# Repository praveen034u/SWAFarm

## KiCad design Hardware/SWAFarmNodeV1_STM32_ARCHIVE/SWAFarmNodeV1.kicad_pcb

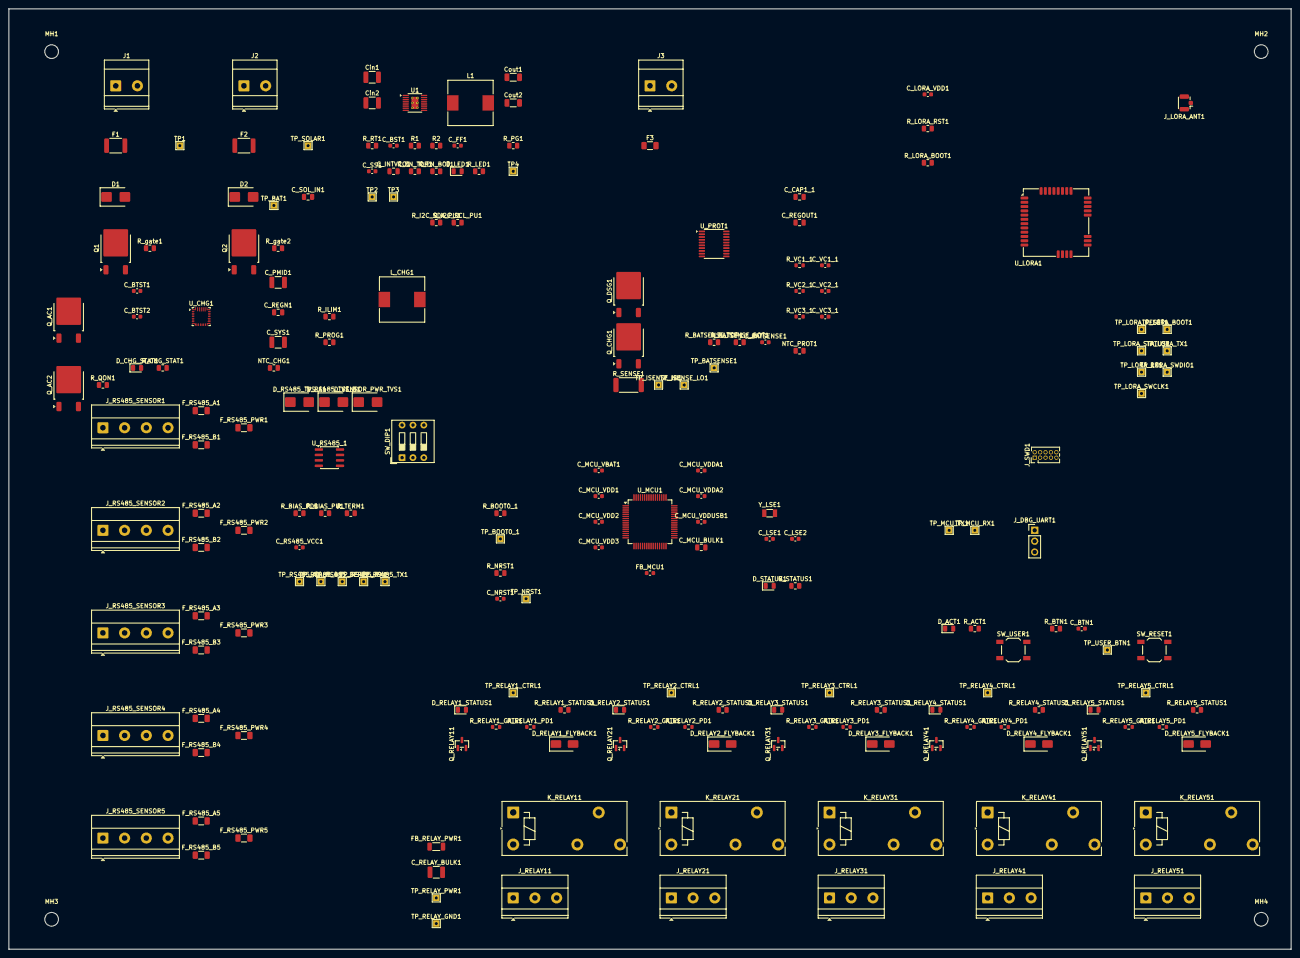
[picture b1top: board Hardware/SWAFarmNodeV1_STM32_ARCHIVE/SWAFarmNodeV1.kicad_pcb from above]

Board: 4 copper layers, 300.0 x 220.0 mm, 203 parts (0 on the bottom side), 138 nets, no tracks yet.

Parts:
C_BATSENSE1: 100nF; C_0603_1608Metric
C_BST1: 0.1uF; C_0603_1608Metric
C_BTN1: 100nF; C_0603_1608Metric
C_BTST1, C_BTST2: 100nF; C_0603_1608Metric
C_CAP1_1: 1uF; C_0805_2012Metric
C_FF1: 10pF; C_0603_1608Metric
C_INTVCC1: 2.2uF; C_0805_2012Metric
C_LORA_VDD1: 100nF; C_0603_1608Metric
C_LSE1, C_LSE2: 8pF; C_0603_1608Metric
C_MCU_BULK1: 4.7uF; C_0805_2012Metric
C_MCU_VBAT1: 100nF; C_0603_1608Metric
C_MCU_VDD1, C_MCU_VDD2, C_MCU_VDD3: 100nF; C_0603_1608Metric
C_MCU_VDDA1: 1uF; C_0603_1608Metric
C_MCU_VDDA2: 100nF; C_0603_1608Metric
C_MCU_VDDUSB1: 100nF; C_0603_1608Metric
C_NRST1: 100nF; C_0603_1608Metric
C_PMID1: 10uF; C_1210_3225Metric
C_REGN1: 1uF; C_0805_2012Metric
C_REGOUT1: 1uF; C_0805_2012Metric
C_RELAY_BULK1: 22uF; C_1210_3225Metric
C_RS485_VCC1: 100nF; C_0603_1608Metric
C_SOL_IN1: 4.7uF; C_0805_2012Metric
C_SS1: 10nF; C_0603_1608Metric
C_SYS1: 22uF; C_1210_3225Metric
C_VC1_1, C_VC2_1, C_VC3_1: 100nF; C_0603_1608Metric
Cin1, Cin2: 10uF_50V; C_1210_3225Metric
Cout1, Cout2: 22uF_16V; C_1206_3216Metric
D1: SMBJ16CA; D_SMB
D2: SMBJ24A_class_unidirectional; D_SMB
D_ACT1: LED_Yellow_activity; LED_0805_2012Metric
D_CHG_STAT1: LED_Yellow_charge_status; LED_0805_2012Metric
D_LED1: LED_Green_2mA; LED_0805_2012Metric
D_RELAY1_FLYBACK1, D_RELAY2_FLYBACK1, D_RELAY3_FLYBACK1, D_RELAY4_FLYBACK1, D_RELAY5_FLYBACK1: S1M_1A_1000V_SMA; D_SMA
D_RELAY1_STATUS1, D_RELAY2_STATUS1, D_RELAY3_STATUS1, D_RELAY4_STATUS1, D_RELAY5_STATUS1: LED_Green_relay_status; LED_0805_2012Metric
D_RS485_TVS_A1, D_RS485_TVS_B1: SMBJ_class_RS485; D_SMB
D_SENSOR_PWR_TVS1: SMBJ18A_class_unidirectional; D_SMB
D_STATUS1: LED_Green_status; LED_0805_2012Metric
F1: 1.1A_Hold_PTC; Fuse_1812_4532Metric
F2: 0.75A_Hold_PTC; Fuse_1812_4532Metric
F3: 10A_series_onetime; Fuse_1206_3216Metric
FB_MCU1: BLM18 class; L_0603_1608Metric
FB_RELAY_PWR1: Power Ferrite, 1A class; L_1206_3216Metric
F_RS485_A1, F_RS485_A2, F_RS485_A3, F_RS485_A4, F_RS485_A5, F_RS485_B1, F_RS485_B2, F_RS485_B3, F_RS485_B4, F_RS485_B5, F_RS485_PWR1, F_RS485_PWR2, F_RS485_PWR3, F_RS485_PWR4, F_RS485_PWR5: 0.2A_Hold_PTC; Fuse_1206_3216Metric
J1: DC_IN_12V; TerminalBlock_Phoenix_MKDS-3-2-5.08_1x02_P5.08mm_Horizontal
J2: SOLAR_IN_12V_class; TerminalBlock_Phoenix_MKDS-3-2-5.08_1x02_P5.08mm_Horizontal
J3: 4S_LiFePO4_Pack; TerminalBlock_Phoenix_MKDS-3-2-5.08_1x02_P5.08mm_Horizontal
J_DBG_UART1: Debug_Console; PinHeader_1x03_P2.54mm_Vertical
J_LORA_ANT1: U.FL_to_SMA_pigtail; U.FL_Hirose_U.FL-R-SMT-1_Vertical
J_RELAY11: Relay1_COM_NO_NC; TerminalBlock_Phoenix_MKDS-1,5-3-5.08_1x03_P5.08mm_Horizont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
J_RELAY21: Relay2_COM_NO_NC; TerminalBlock_Phoenix_MKDS-1,5-3-5.08_1x03_P5.08mm_Horizont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
J_RELAY31: Relay3_COM_NO_NC; TerminalBlock_Phoenix_MKDS-1,5-3-5.08_1x03_P5.08mm_Horizont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
J_RELAY41: Relay4_COM_NO_NC; TerminalBlock_Phoenix_MKDS-1,5-3-5.08_1x03_P5.08mm_Horizont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
J_RELAY51: Relay5_COM_NO_NC; TerminalBlock_Phoenix_MKDS-1,5-3-5.08_1x03_P5.08mm_Horizont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
J_RS485_SENSOR1: Sensor1_A_B_PWR_GND; TerminalBlock_Phoenix_MKDS-1,5-4-5.08_1x04_P5.08mm_Horizont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
J_RS485_SENSOR2: Sensor2_A_B_PWR_GND; TerminalBlock_Phoenix_MKDS-1,5-4-5.08_1x04_P5.08mm_Horizont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
J_RS485_SENSOR3: Sensor3_A_B_PWR_GND; TerminalBlock_Phoenix_MKDS-1,5-4-5.08_1x04_P5.08mm_Horizont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
J_RS485_SENSOR4: Sensor4_A_B_PWR_GND; TerminalBlock_Phoenix_MKDS-1,5-4-5.08_1x04_P5.08mm_Horizont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
J_RS485_SENSOR5: Sensor5_A_B_PWR_GND; TerminalBlock_Phoenix_MKDS-1,5-4-5.08_1x04_P5.08mm_Horizont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
J_SWD1: SWD_ARM10; PinHeader_2x05_P1.27mm_Vertical
K_RELAY11, K_RELAY21, K_RELAY31, K_RELAY41, K_RELAY51: FINDER-40.51.9.012.0000_12VDC_SPDT_10A; Relay_SPDT_Finder_40.51
L1: 4.7uH; L_10.4x10.4_H4.8
L_CHG1: 2.2uH_5A_class; L_10.4x10.4_H4.8
MH1, MH2, MH3, MH4: MountingHole_3.2mm_M3
NTC_CHG1: 10k_NTC_-20to60C_class; R_0805_2012Metric
NTC_PROT1: 10k_NTC_-20to60C_class; R_0805_2012Metric
Q1, Q2: NMOS_30V_RDSon_20mOhm; TO-252-2
Q_AC1, Q_AC2: NMOS_30V_RDSon_20mOhm; TO-252-2
Q_CHG1: NMOS_30V_RDSon_20mOhm; TO-252-2
Q_DSG1: NMOS_30V_RDSon_20mOhm; TO-252-2
Q_RELAY11, Q_RELAY21, Q_RELAY31, Q_RELAY41, Q_RELAY51: NMOS_30V_RDSon_100mOhm_SOT23; SOT-23
R1: 24.0k_1%; R_0805_2012Metric
R2: 10.0k_1%; R_0805_2012Metric
R_ACT1: 1k; R_0805_2012Metric
R_BATSENSE_BOT1: 180k; R_0805_2012Metric
R_BATSENSE_TOP1: 680k; R_0805_2012Metric
R_BIAS_PD1: 560; R_0805_2012Metric
R_BIAS_PU1: 560; R_0805_2012Metric
R_BOOT0_1: 10k; R_0805_2012Metric
R_BTN1: 10k; R_0805_2012Metric
R_CHG_STAT1: 1k; R_0805_2012Metric
R_EN_BOT1: 100k; R_0805_2012Metric
R_EN_TOP1: 787k; R_0805_2012Metric
R_I2C_SCL_PU1, R_I2C_SDA_PU1: 4.7k; R_0805_2012Metric
R_ILIM1: TBD_verify_datasheet_ILIM_formula; R_0805_2012Metric
R_LED1: 680; R_0805_2012Metric
R_LORA_BOOT1: 10k; R_0805_2012Metric
R_LORA_RST1: 10k; R_0805_2012Metric
R_NRST1: 10k; R_0805_2012Metric
R_PG1: 100k; R_0805_2012Metric
R_PROG1: TBD_verify_datasheet_for_1.6A_target; R_0805_2012Metric
R_QON1: 100k; R_0805_2012Metric
R_RELAY1_GATE1, R_RELAY2_GATE1, R_RELAY3_GATE1, R_RELAY4_GATE1, R_RELAY5_GATE1: 100; R_0603_1608Metric
R_RELAY1_PD1, R_RELAY2_PD1, R_RELAY3_PD1, R_RELAY4_PD1, R_RELAY5_PD1: 10k; R_0603_1608Metric
R_RELAY1_STATUS1, R_RELAY2_STATUS1, R_RELAY3_STATUS1, R_RELAY4_STATUS1, R_RELAY5_STATUS1: 1k; R_0805_2012Metric
R_RT1: 41.2k; R_0805_2012Metric
R_SENSE1: 5mOhm_1percent_2512; R_2512_6332Metric
R_STATUS1: 330; R_0805_2012Metric
R_TERM1: 120; R_0805_2012Metric
R_VC1_1, R_VC2_1, R_VC3_1: 1k; R_0603_1608Metric
R_gate1, R_gate2: 10k; R_0805_2012Metric
SW_DIP1: TERM_BIAS_SELECT; SW_DIP_SPSTx03_Slide_9.78x9.8mm_W7.62mm_P2.54mm
SW_RESET1: Reset_Button; SW_SPST_TL3342
SW_USER1: User_Button; SW_SPST_TL3342
TP1: VIN_PROT; TestPoint_THTPad_1.5x1.5mm_Drill0.7mm
TP2: 3V3_RAIL; TestPoint_THTPad_1.5x1.5mm_Drill0.7mm
TP3: GND; TestPoint_THTPad_1.5x1.5mm_Drill0.7mm
TP4: PG; TestPoint_THTPad_1.5x1.5mm_Drill0.7mm
TP_BAT1: BAT_P; TestPoint_THTPad_1.5x1.5mm_Drill0.7mm
TP_BATSENSE1: BATSENSE_MID; TestPoint_THTPad_1.5x1.5mm_Drill0.7mm
TP_BOOT0_1: BOOT0; TestPoint_THTPad_1.5x1.5mm_Drill0.7mm
TP_ISENSE_HI1: SRP; TestPoint_THTPad_1.5x1.5mm_Drill0.7mm
TP_ISENSE_LO1: SRN_GND; TestPoint_THTPad_1.5x1.5mm_Drill0.7mm
TP_LORA_BOOT1: LORA_BOOT0; TestPoint_THTPad_1.5x1.5mm_Drill0.7mm
TP_LORA_RESET1: LORA_RESET_N; TestPoint_THTPad_1.5x1.5mm_Drill0.7mm
TP_LORA_RX1: LORA_RX; TestPoint_THTPad_1.5x1.5mm_Drill0.7mm
TP_LORA_STATUS1: LORA_STATUS; TestPoint_THTPad_1.5x1.5mm_Drill0.7mm
TP_LORA_SWCLK1: LORA_SWCLK; TestPoint_THTPad_1.5x1.5mm_Drill0.7mm
TP_LORA_SWDIO1: LORA_SWDIO; TestPoint_THTPad_1.5x1.5mm_Drill0.7mm
TP_LORA_TX1: LORA_TX; TestPoint_THTPad_1.5x1.5mm_Drill0.7mm
TP_MCU_RX1: MCU_RX; TestPoint_THTPad_1.5x1.5mm_Drill0.7mm
TP_MCU_TX1: MCU_TX; TestPoint_THTPad_1.5x1.5mm_Drill0.7mm
TP_NRST1: NRST; TestPoint_THTPad_1.5x1.5mm_Drill0.7mm
TP_RELAY1_CTRL1: RELAY1_CTRL; TestPoint_THTPad_1.5x1.5mm_Drill0.7mm
TP_RELAY2_CTRL1: RELAY2_CTRL; TestPoint_THTPad_1.5x1.5mm_Drill0.7mm
TP_RELAY3_CTRL1: RELAY3_CTRL; TestPoint_THTPad_1.5x1.5mm_Drill0.7mm
TP_RELAY4_CTRL1: RELAY4_CTRL; TestPoint_THTPad_1.5x1.5mm_Drill0.7mm
TP_RELAY5_CTRL1: RELAY5_CTRL; TestPoint_THTPad_1.5x1.5mm_Drill0.7mm
TP_RELAY_GND1: GND; TestPoint_THTPad_1.5x1.5mm_Drill0.7mm
TP_RELAY_PWR1: RELAY_PWR; TestPoint_THTPad_1.5x1.5mm_Drill0.7mm
TP_RS485_A1: RS485_A; TestPoint_THTPad_1.5x1.5mm_Drill0.7mm
TP_RS485_B1: RS485_B; TestPoint_THTPad_1.5x1.5mm_Drill0.7mm
TP_RS485_DERE1: RS485_DE_RE; TestPoint_THTPad_1.5x1.5mm_Drill0.7mm
TP_RS485_RX1: RS485_RX; TestPoint_THTPad_1.5x1.5mm_Drill0.7mm
TP_RS485_TX1: RS485_TX; TestPoint_THTPad_1.5x1.5mm_Drill0.7mm
TP_SOLAR1: SOL_PROT; TestPoint_THTPad_1.5x1.5mm_Drill0.7mm
TP_USER_BTN1: USER_BTN; TestPoint_THTPad_1.5x1.5mm_Drill0.7mm
U1: LT8610AC-3.3; MSOP-16-1EP_3x4.039mm_P0.5mm_EP1.651x2.845mm_ThermalVias
U_CHG1: BQ25798_substitutes_BQ25792; Texas_RQM0029A_VQFN-29_4x4mm_P0.4mm
U_LORA1: RAK3172-IN865; RAK3172
U_MCU1: STM32L462RETx; LQFP-64_10x10mm_P0.5mm
U_PROT1: BQ76920PW; TSSOP-20_4.4x6.5mm_P0.65mm
U_RS485_1: THVD1450D; SOIC-8_3.9x4.9mm_P1.27mm
Y_LSE1: 32.768kHz; Crystal_SMD_3215-2Pin_3.2x1.5mm

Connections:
/3V3_RAIL: C_FF1.1, C_LORA_VDD1.1, C_MCU_BULK1.1, C_MCU_VBAT1.1, C_MCU_VDD1.1, C_MCU_VDD2.1, C_MCU_VDD3.1, C_MCU_VDDUSB1.1, C_RS485_VCC1.1, Cout1.1, Cout2.1, FB_MCU1.1, J_SWD1.1, L1.1, R1.1, R_BIAS_PU1.2, R_BTN1.1, R_CHG_STAT1.1, R_I2C_SCL_PU1.1, R_I2C_SDA_PU1.1, R_LED1.1, R_LORA_RST1.1, R_NRST1.1, R_PG1.1, TP2.1, U1.14, U_LORA1.24, U_MCU1.1, U_MCU1.19, U_MCU1.32, U_MCU1.48, U_MCU1.64, U_RS485_1.8
/ACTIVITY_LED: R_ACT1.1, U_MCU1.39
/BATSENSE_MID: C_BATSENSE1.1, R_BATSENSE_BOT1.1, R_BATSENSE_TOP1.2, TP_BATSENSE1.1, U_MCU1.27
/BAT_P: F3.2, R_BATSENSE_TOP1.1, TP_BAT1.1, U_CHG1.18, U_CHG1.22, U_CHG1.23, U_PROT1.9, U_PROT1.10, U_PROT1.12, U_PROT1.13
/BOOT0: R_BOOT0_1.1, TP_BOOT0_1.1, U_MCU1.60
/BTST1_NODE: C_BTST1.1, U_CHG1.4
/BTST2_NODE: C_BTST2.1, U_CHG1.19
/CAP1_NODE: C_CAP1_1.1, U_PROT1.7
/CELL_N: J3.2, Q_DSG1.3, U_PROT1.17
/CELL_TAP1: R_VC1_1.1, U_PROT1.16
/CELL_TAP1_FILT: C_VC1_1.1, R_VC1_1.2
/CELL_TAP2: R_VC2_1.1, U_PROT1.15
/CELL_TAP2_FILT: C_VC2_1.1, R_VC2_1.2
/CELL_TAP3: R_VC3_1.1, U_PROT1.14
/CELL_TAP3_FILT: C_VC3_1.1, R_VC3_1.2
/CHG_ALERT_N: U_CHG1.21, U_MCU1.24
/CHG_STAT: D_CHG_STAT1.2, R_CHG_STAT1.2, U_CHG1.1
/CHG_VBUS_INT: C_BTST1.2, C_BTST2.2, Q_AC1.2, Q_AC2.2, U_CHG1.2, U_CHG1.3
/DC_IN_RAW_N: J1.2, Q1.3
/DC_IN_RAW_P: F1.1, J1.1
/FET_MID: Q_CHG1.2, Q_DSG1.2
/J3_BAT_P_RAW: F3.1, J3.1
/LORA_BOOT0: R_LORA_BOOT1.1, TP_LORA_BOOT1.1, U_LORA1.21
/LORA_RESET_N: R_LORA_RST1.2, TP_LORA_RESET1.1, U_LORA1.22, U_MCU1.14
/LORA_RX: TP_LORA_RX1.1, U_LORA1.4, U_MCU1.17
/LORA_STATUS: TP_LORA_STATUS1.1, U_LORA1.32, U_MCU1.15
/LORA_SWCLK: TP_LORA_SWCLK1.1, U_LORA1.8
/LORA_SWDIO: TP_LORA_SWDIO1.1, U_LORA1.7
/LORA_TX: TP_LORA_TX1.1, U_LORA1.5, U_MCU1.16
/MCU_RX: J_DBG_UART1.3, TP_MCU_RX1.1, U_MCU1.43
/MCU_TX: J_DBG_UART1.2, TP_MCU_TX1.1, U_MCU1.42
/NET_CHG_GATE: Q_CHG1.1, U_PROT1.2
/NET_CHG_SW1: L_CHG1.1, U_CHG1.28
/NET_CHG_SW2: L_CHG1.2, U_CHG1.26
/NET_DSG_GATE: Q_DSG1.1, U_PROT1.1
/NET_ILIM_HIZ: R_ILIM1.1, U_CHG1.17
/NET_PROG: R_PROG1.1, U_CHG1.20
/NET_Q2_GATE: Q2.1, R_gate2.2
/NET_QAC1_GATE: Q_AC1.1, U_CHG1.11
/NET_QAC2_GATE: Q_AC2.1, U_CHG1.10
/NET_QON: R_QON1.1, U_CHG1.12
/NRST: C_NRST1.1, J_SWD1.10, R_NRST1.2, SW_RESET1.1, TP_NRST1.1, U_MCU1.7
/NTC_CHG_NODE: NTC_CHG1.1, U_CHG1.16
/NTC_PROT_NODE: NTC_PROT1.1, U_PROT1.6
/OSC32_IN: C_LSE1.1, U_MCU1.3, Y_LSE1.1
/OSC32_OUT: C_LSE2.1, U_MCU1.4, Y_LSE1.2
/PG: R_PG1.2, TP4.1, U1.15
/PMID_NODE: C_PMID1.1, U_CHG1.29
/PROT_ALERT_N: U_MCU1.25, U_PROT1.20
/PWR_I2C_SCL: R_I2C_SCL_PU1.2, U_CHG1.14, U_MCU1.61, U_PROT1.5
/PWR_I2C_SDA: R_I2C_SDA_PU1.2, U_CHG1.15, U_MCU1.62, U_PROT1.4
/REGN_NODE: C_REGN1.1, U_CHG1.5
/REGOUT_NODE: C_REGOUT1.1, U_PROT1.8
/RELAY1_COIL_RTN: D_RELAY1_FLYBACK1.2, K_RELAY11.A2, Q_RELAY11.3
/RELAY1_COM: J_RELAY11.1, K_RELAY11.11
/RELAY1_CTRL: R_RELAY1_GATE1.1, R_RELAY1_STATUS1.1, TP_RELAY1_CTRL1.1, U_MCU1.33
/RELAY1_GATE: Q_RELAY11.1, R_RELAY1_GATE1.2, R_RELAY1_PD1.1
/RELAY1_LED_A: D_RELAY1_STATUS1.2, R_RELAY1_STATUS1.2
/RELAY1_NC: J_RELAY11.3, K_RELAY11.12
/RELAY1_NO: J_RELAY11.2, K_RELAY11.14
/RELAY2_COIL_RTN: D_RELAY2_FLYBACK1.2, K_RELAY21.A2, Q_RELAY21.3
/RELAY2_COM: J_RELAY21.1, K_RELAY21.11
/RELAY2_CTRL: R_RELAY2_GATE1.1, R_RELAY2_STATUS1.1, TP_RELAY2_CTRL1.1, U_MCU1.34
/RELAY2_GATE: Q_RELAY21.1, R_RELAY2_GATE1.2, R_RELAY2_PD1.1
/RELAY2_LED_A: D_RELAY2_STATUS1.2, R_RELAY2_STATUS1.2
/RELAY2_NC: J_RELAY21.3, K_RELAY21.12
/RELAY2_NO: J_RELAY21.2, K_RELAY21.14
/RELAY3_COIL_RTN: D_RELAY3_FLYBACK1.2, K_RELAY31.A2, Q_RELAY31.3
/RELAY3_COM: J_RELAY31.1, K_RELAY31.11
/RELAY3_CTRL: R_RELAY3_GATE1.1, R_RELAY3_STATUS1.1, TP_RELAY3_CTRL1.1, U_MCU1.35
/RELAY3_GATE: Q_RELAY31.1, R_RELAY3_GATE1.2, R_RELAY3_PD1.1
/RELAY3_LED_A: D_RELAY3_STATUS1.2, R_RELAY3_STATUS1.2
/RELAY3_NC: J_RELAY31.3, K_RELAY31.12
/RELAY3_NO: J_RELAY31.2, K_RELAY31.14
/RELAY4_COIL_RTN: D_RELAY4_FLYBACK1.2, K_RELAY41.A2, Q_RELAY41.3
/RELAY4_COM: J_RELAY41.1, K_RELAY41.11
/RELAY4_CTRL: R_RELAY4_GATE1.1, R_RELAY4_STATUS1.1, TP_RELAY4_CTRL1.1, U_MCU1.36
/RELAY4_GATE: Q_RELAY41.1, R_RELAY4_GATE1.2, R_RELAY4_PD1.1
/RELAY4_LED_A: D_RELAY4_STATUS1.2, R_RELAY4_STATUS1.2
/RELAY4_NC: J_RELAY41.3, K_RELAY41.12
/RELAY4_NO: J_RELAY41.2, K_RELAY41.14
/RELAY5_COIL_RTN: D_RELAY5_FLYBACK1.2, K_RELAY51.A2, Q_RELAY51.3
/RELAY5_COM: J_RELAY51.1, K_RELAY51.11
/RELAY5_CTRL: R_RELAY5_GATE1.1, R_RELAY5_STATUS1.1, TP_RELAY5_CTRL1.1, U_MCU1.50
/RELAY5_GATE: Q_RELAY51.1, R_RELAY5_GATE1.2, R_RELAY5_PD1.1
/RELAY5_LED_A: D_RELAY5_STATUS1.2, R_RELAY5_STATUS1.2
/RELAY5_NC: J_RELAY51.3, K_RELAY51.12
/RELAY5_NO: J_RELAY51.2, K_RELAY51.14
/RELAY_PWR: C_RELAY_BULK1.1, D_RELAY1_FLYBACK1.1, D_RELAY2_FLYBACK1.1, D_RELAY3_FLYBACK1.1, D_RELAY4_FLYBACK1.1, D_RELAY5_FLYBACK1.1, FB_RELAY_PWR1.2, K_RELAY11.A1, K_RELAY21.A1, K_RELAY31.A1, K_RELAY41.A1, K_RELAY51.A1, TP_RELAY_PWR1.1
/RS485_A: D_RS485_TVS_A1.1, F_RS485_A1.1, F_RS485_A2.1, F_RS485_A3.1, F_RS485_A4.1, F_RS485_A5.1, R_TERM1.2, SW_DIP1.5, TP_RS485_A1.1, U_RS485_1.6
/RS485_A_RAW1: F_RS485_A1.2, J_RS485_SENSOR1.1
/RS485_A_RAW2: F_RS485_A2.2, J_RS485_SENSOR2.1
/RS485_A_RAW3: F_RS485_A3.2, J_RS485_SENSOR3.1
/RS485_A_RAW4: F_RS485_A4.2, J_RS485_SENSOR4.1
/RS485_A_RAW5: F_RS485_A5.2, J_RS485_SENSOR5.1
/RS485_B: D_RS485_TVS_B1.1, F_RS485_B1.1, F_RS485_B2.1, F_RS485_B3.1, F_RS485_B4.1, F_RS485_B5.1, SW_DIP1.4, SW_DIP1.6, TP_RS485_B1.1, U_RS485_1.7
/RS485_B_RAW1: F_RS485_B1.2, J_RS485_SENSOR1.2
/RS485_B_RAW2: F_RS485_B2.2, J_RS485_SENSOR2.2
/RS485_B_RAW3: F_RS485_B3.2, J_RS485_SENSOR3.2
/RS485_B_RAW4: F_RS485_B4.2, J_RS485_SENSOR4.2
/RS485_B_RAW5: F_RS485_B5.2, J_RS485_SENSOR5.2
/RS485_DE_RE: TP_RS485_DERE1.1, U_MCU1.28, U_RS485_1.2, U_RS485_1.3
/RS485_RX: TP_RS485_RX1.1, U_MCU1.30, U_RS485_1.1
/RS485_TX: TP_RS485_TX1.1, U_MCU1.29, U_RS485_1.4
/SENSE_SRP: Q_CHG1.3, R_SENSE1.1, TP_ISENSE_HI1.1, U_PROT1.18
/SOL_IN_RAW_N: J2.2, Q2.3
/SOL_IN_RAW_P: F2.1, J2.1
/SOL_PROT: C_SOL_IN1.1, D2.1, F2.2, Q_AC2.3, R_gate2.1, TP_SOLAR1.1, U_CHG1.8
/STATUS_LED: R_STATUS1.1, U_MCU1.2
/SWCLK: J_SWD1.4, U_MCU1.49
/SWDIO: J_SWD1.2, U_MCU1.46
/SWO: J_SWD1.6, U_MCU1.55
/USER_BTN: C_BTN1.1, R_BTN1.2, SW_USER1.1, TP_USER_BTN1.1, U_MCU1.37
/VDDA: C_MCU_VDDA1.1, C_MCU_VDDA2.1, FB_MCU1.2, U_MCU1.13
/VIN_PROT: Cin1.1, Cin2.1, D1.1, F1.2, Q_AC1.3, R_EN_TOP1.1, R_gate1.1, TP1.1, U_CHG1.9
/VSYS: C_SYS1.1, U1.5, U1.6, U_CHG1.25
/VSYS_RAW_OUT: D_SENSOR_PWR_TVS1.1, FB_RELAY_PWR1.1, F_RS485_PWR1.1, F_RS485_PWR2.1, F_RS485_PWR3.1, F_RS485_PWR4.1, F_RS485_PWR5.1
/VSYS_RAW_OUT1: F_RS485_PWR1.2, J_RS485_SENSOR1.3
/VSYS_RAW_OUT2: F_RS485_PWR2.2, J_RS485_SENSOR2.3
/VSYS_RAW_OUT3: F_RS485_PWR3.2, J_RS485_SENSOR3.3
/VSYS_RAW_OUT4: F_RS485_PWR4.2, J_RS485_SENSOR4.3
/VSYS_RAW_OUT5: F_RS485_PWR5.2, J_RS485_SENSOR5.3
GND: C_BATSENSE1.2, C_BTN1.2, C_CAP1_1.2, C_INTVCC1.1, C_LORA_VDD1.2, C_LSE1.2, C_LSE2.2, C_MCU_BULK1.2, C_MCU_VBAT1.2, C_MCU_VDD1.2, C_MCU_VDD2.2, C_MCU_VDD3.2, C_MCU_VDDA1.2, C_MCU_VDDA2.2, C_MCU_VDDUSB1.2, C_NRST1.2, C_PMID1.2, C_REGN1.2, C_REGOUT1.2, C_RELAY_BULK1.2, C_RS485_VCC1.2, C_SOL_IN1.2, C_SS1.2, C_SYS1.2, C_VC1_1.2, C_VC2_1.2, C_VC3_1.2, Cin1.2, Cin2.2, Cout1.2, Cout2.2, D1.2, D2.2, D_ACT1.1, D_CHG_STAT1.1, D_LED1.1, D_RELAY1_STATUS1.1, D_RELAY2_STATUS1.1, D_RELAY3_STATUS1.1, D_RELAY4_STATUS1.1, D_RELAY5_STATUS1.1, D_RS485_TVS_A1.2, D_RS485_TVS_B1.2, D_SENSOR_PWR_TVS1.2, D_STATUS1.1, J_DBG_UART1.1, J_LORA_ANT1.2, J_RS485_SENSOR1.4, J_RS485_SENSOR2.4, J_RS485_SENSOR3.4, J_RS485_SENSOR4.4, J_RS485_SENSOR5.4, J_SWD1.3, J_SWD1.5, J_SWD1.9, NTC_CHG1.2, NTC_PROT1.2, Q1.2, Q2.2, Q_RELAY11.2, Q_RELAY21.2, Q_RELAY31.2, Q_RELAY41.2, Q_RELAY51.2, R2.2, R_BATSENSE_BOT1.2, R_BIAS_PD1.2, R_BOOT0_1.2, R_EN_BOT1.2, R_ILIM1.2, R_LORA_BOOT1.2, R_PROG1.2, R_QON1.2, R_RELAY1_PD1.2, R_RELAY2_PD1.2, R_RELAY3_PD1.2, R_RELAY4_PD1.2, R_RELAY5_PD1.2, R_RT1.2, R_SENSE1.2, SW_RESET1.2, SW_USER1.2, TP3.1, TP_ISENSE_LO1.1, TP_RELAY_GND1.1, U1.1, U1.8, U1.17, U_CHG1.13, U_CHG1.27, U_LORA1.11, U_LORA1.17, U_LORA1.18, U_LORA1.23, U_LORA1.28, U_MCU1.12, U_MCU1.18, U_MCU1.31, U_MCU1.47, U_MCU1.63, U_PROT1.3, U_PROT1.19, U_RS485_1.5
unnamed: C_BST1.2, L1.2, U1.9, U1.10, U1.11
unnamed: D_ACT1.2, R_ACT1.2
unnamed: D_LED1.2, R_LED1.2
unnamed: D_STATUS1.2, R_STATUS1.2
unnamed: J_LORA_ANT1.1, U_LORA1.12
unnamed: Q1.1, R_gate1.2
unnamed: R_BIAS_PD1.1, SW_DIP1.3
unnamed: R_BIAS_PU1.1, SW_DIP1.2
unnamed: R_TERM1.1, SW_DIP1.1
unnamed: C_BST1.1, U1.12
unnamed: R_EN_BOT1.1, R_EN_TOP1.2, U1.4
unnamed: C_FF1.2, R1.2, R2.1, U1.16
unnamed: C_INTVCC1.2, U1.13
unnamed: R_RT1.1, U1.3
unnamed: C_SS1.1, U1.2

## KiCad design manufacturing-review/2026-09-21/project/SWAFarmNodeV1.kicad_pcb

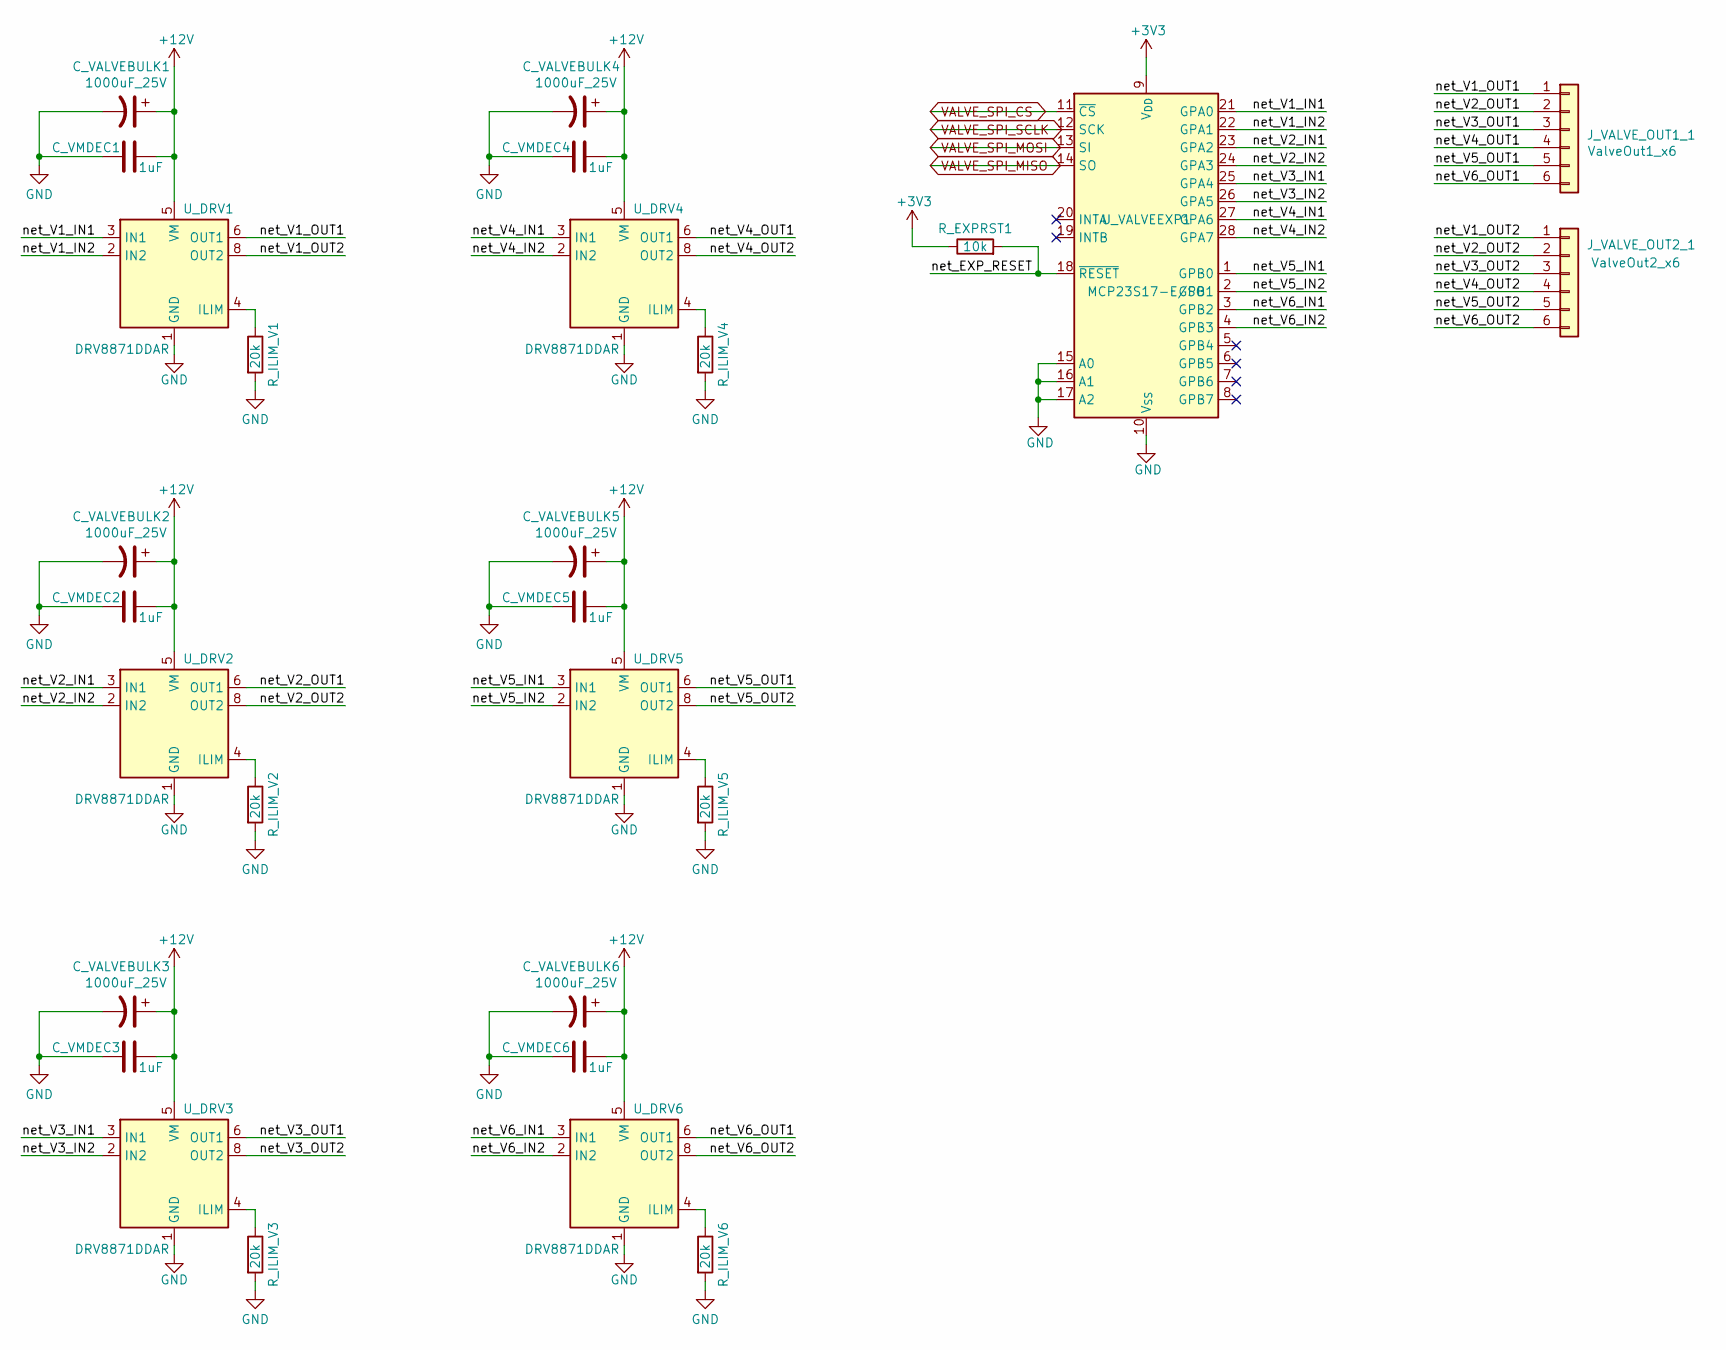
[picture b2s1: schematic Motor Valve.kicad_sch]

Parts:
C_VALVEBULK1, C_VALVEBULK2, C_VALVEBULK3, C_VALVEBULK4, C_VALVEBULK5, C_VALVEBULK6: 1000uF_25V; CP_Radial_D10.0mm_P5.00mm; MPN EEUFR1E102
C_VMDEC1, C_VMDEC2, C_VMDEC3, C_VMDEC4, C_VMDEC5, C_VMDEC6: 1uF; C_0805_2012Metric
J_VALVE_OUT1_1: ValveOut1_x6; TerminalBlock_Phoenix_MKDS-1,5-6-5.08_1x06_P5.08mm_Horizont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
J_VALVE_OUT2_1: ValveOut2_x6; TerminalBlock_Phoenix_MKDS-1,5-6-5.08_1x06_P5.08mm_Horizont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
R_EXPRST1: 10k; R_0805_2012Metric
R_ILIM_V1, R_ILIM_V2, R_ILIM_V3, R_ILIM_V4, R_ILIM_V5, R_ILIM_V6: 20k; R_0805_2012Metric
U_DRV1, U_DRV2, U_DRV3, U_DRV4, U_DRV5, U_DRV6: DRV8871DDAR; TI_SO-PowerPAD-8_ThermalVias
U_VALVEEXP1: MCP23S17-E/SO; SOIC-28W_7.5x17.9mm_P1.27mm

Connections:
+3V3: R_EXPRST1.1, U_VALVEEXP1.9 (V_{DD}); also elsewhere on the board
+12V: C_VALVEBULK1.1, C_VALVEBULK2.1, C_VALVEBULK3.1, C_VALVEBULK4.1, C_VALVEBULK5.1, C_VALVEBULK6.1, C_VMDEC1.1, C_VMDEC2.1, C_VMDEC3.1, C_VMDEC4.1, C_VMDEC5.1, C_VMDEC6.1, U_DRV1.5 (VM), U_DRV2.5 (VM), U_DRV3.5 (VM), U_DRV4.5 (VM), U_DRV5.5 (VM), U_DRV6.5 (VM); also elsewhere on the board
/Motor Valve/net_EXP_RESET: R_EXPRST1.2, U_VALVEEXP1.18 (~RESET)
/Motor Valve/net_V1_IN1: U_DRV1.3 (IN1), U_VALVEEXP1.21 (GPA0)
/Motor Valve/net_V1_IN2: U_DRV1.2 (IN2), U_VALVEEXP1.22 (GPA1)
/Motor Valve/net_V1_OUT1: J_VALVE_OUT1_1.1, U_DRV1.6 (OUT1)
/Motor Valve/net_V1_OUT2: J_VALVE_OUT2_1.1, U_DRV1.8 (OUT2)
/Motor Valve/net_V2_IN1: U_DRV2.3 (IN1), U_VALVEEXP1.23 (GPA2)
/Motor Valve/net_V2_IN2: U_DRV2.2 (IN2), U_VALVEEXP1.24 (GPA3)
/Motor Valve/net_V2_OUT1: J_VALVE_OUT1_1.2, U_DRV2.6 (OUT1)
/Motor Valve/net_V2_OUT2: J_VALVE_OUT2_1.2, U_DRV2.8 (OUT2)
/Motor Valve/net_V3_IN1: U_DRV3.3 (IN1), U_VALVEEXP1.25 (GPA4)
/Motor Valve/net_V3_IN2: U_DRV3.2 (IN2), U_VALVEEXP1.26 (GPA5)
/Motor Valve/net_V3_OUT1: J_VALVE_OUT1_1.3, U_DRV3.6 (OUT1)
/Motor Valve/net_V3_OUT2: J_VALVE_OUT2_1.3, U_DRV3.8 (OUT2)
/Motor Valve/net_V4_IN1: U_DRV4.3 (IN1), U_VALVEEXP1.27 (GPA6)
/Motor Valve/net_V4_IN2: U_DRV4.2 (IN2), U_VALVEEXP1.28 (GPA7)
/Motor Valve/net_V4_OUT1: J_VALVE_OUT1_1.4, U_DRV4.6 (OUT1)
/Motor Valve/net_V4_OUT2: J_VALVE_OUT2_1.4, U_DRV4.8 (OUT2)
/Motor Valve/net_V5_IN1: U_DRV5.3 (IN1), U_VALVEEXP1.1 (GPB0)
/Motor Valve/net_V5_IN2: U_DRV5.2 (IN2), U_VALVEEXP1.2 (GPB1)
/Motor Valve/net_V5_OUT1: J_VALVE_OUT1_1.5, U_DRV5.6 (OUT1)
/Motor Valve/net_V5_OUT2: J_VALVE_OUT2_1.5, U_DRV5.8 (OUT2)
/Motor Valve/net_V6_IN1: U_DRV6.3 (IN1), U_VALVEEXP1.3 (GPB2)
/Motor Valve/net_V6_IN2: U_DRV6.2 (IN2), U_VALVEEXP1.4 (GPB3)
/Motor Valve/net_V6_OUT1: J_VALVE_OUT1_1.6, U_DRV6.6 (OUT1)
/Motor Valve/net_V6_OUT2: J_VALVE_OUT2_1.6, U_DRV6.8 (OUT2)
GND: C_VALVEBULK1.2, C_VALVEBULK2.2, C_VALVEBULK3.2, C_VALVEBULK4.2, C_VALVEBULK5.2, C_VALVEBULK6.2, C_VMDEC1.2, C_VMDEC2.2, C_VMDEC3.2, C_VMDEC4.2, C_VMDEC5.2, C_VMDEC6.2, R_ILIM_V1.2, R_ILIM_V2.2, R_ILIM_V3.2, R_ILIM_V4.2, R_ILIM_V5.2, R_ILIM_V6.2, U_DRV1.1 (GND), U_DRV1.7 (GND), U_DRV1.9 (GND), U_DRV2.1 (GND), U_DRV2.7 (GND), U_DRV2.9 (GND), U_DRV3.1 (GND), U_DRV3.7 (GND), U_DRV3.9 (GND), U_DRV4.1 (GND), U_DRV4.7 (GND), U_DRV4.9 (GND), U_DRV5.1 (GND), U_DRV5.7 (GND), U_DRV5.9 (GND), U_DRV6.1 (GND), U_DRV6.7 (GND), U_DRV6.9 (GND), U_VALVEEXP1.10 (V_{SS}), U_VALVEEXP1.15 (A0), U_VALVEEXP1.16 (A1), U_VALVEEXP1.17 (A2); also elsewhere on the board
unnamed: R_ILIM_V1.1, U_DRV1.4 (ILIM)
unnamed: R_ILIM_V2.1, U_DRV2.4 (ILIM)
unnamed: R_ILIM_V3.1, U_DRV3.4 (ILIM)
unnamed: R_ILIM_V4.1, U_DRV4.4 (ILIM)
unnamed: R_ILIM_V5.1, U_DRV5.4 (ILIM)
unnamed: R_ILIM_V6.1, U_DRV6.4 (ILIM)
VALVE_SPI_CS: U_VALVEEXP1.11 (~CS); also elsewhere on the board
VALVE_SPI_MISO: U_VALVEEXP1.14 (SO); also elsewhere on the board
VALVE_SPI_MOSI: U_VALVEEXP1.13 (SI); also elsewhere on the board
VALVE_SPI_SCLK: U_VALVEEXP1.12 (SCK); also elsewhere on the board

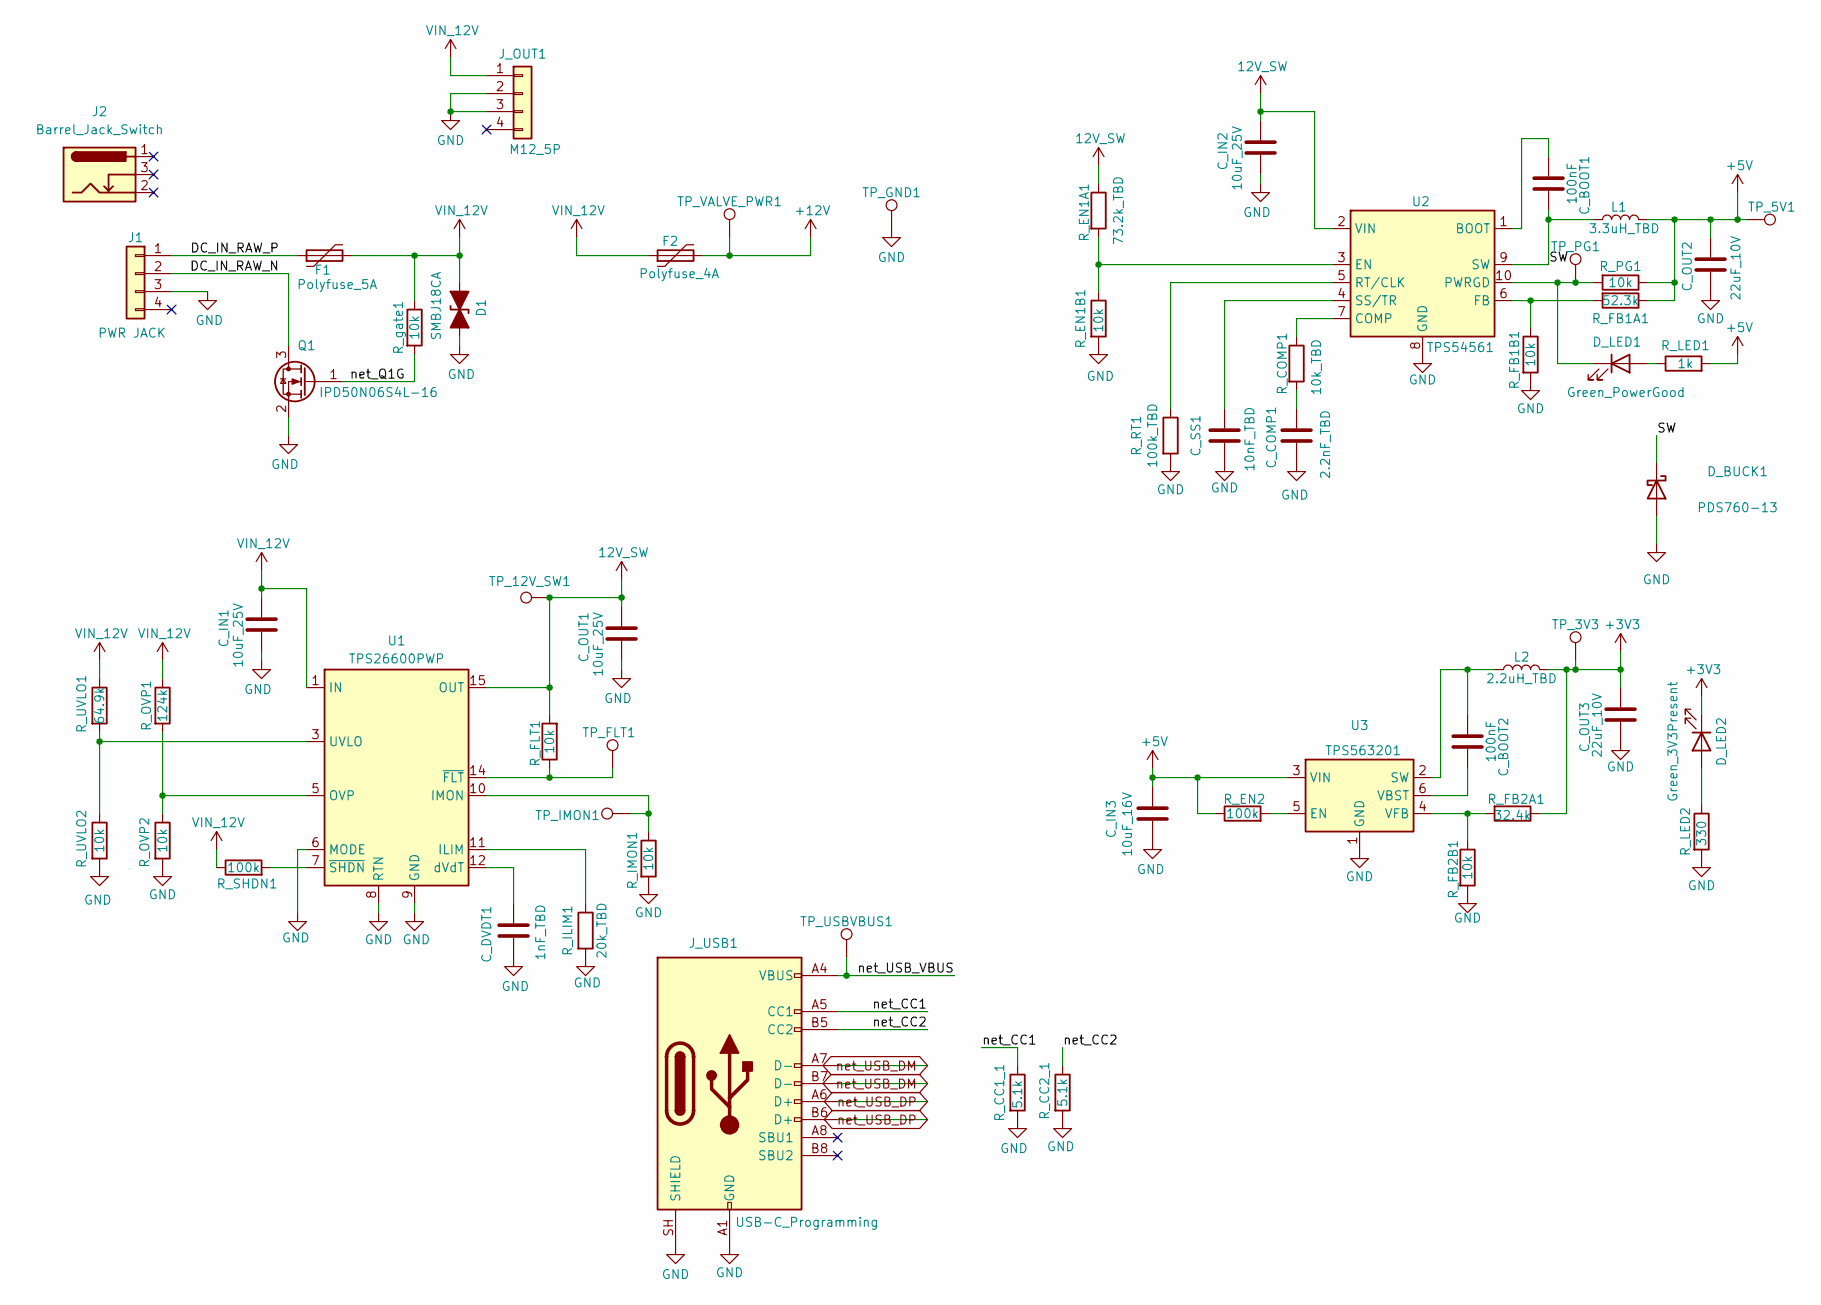
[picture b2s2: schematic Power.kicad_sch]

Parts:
C_BOOT1, C_BOOT2: 100nF; C_0603_1608Metric
C_COMP1: 2.2nF_TBD; C_0603_1608Metric
C_DVDT1: 1nF_TBD; C_0805_2012Metric
C_IN1, C_IN2: 10uF_25V; C_1206_3216Metric
C_IN3: 10uF_16V; C_1206_3216Metric
C_OUT1: 10uF_25V; C_1206_3216Metric
C_OUT2, C_OUT3: 22uF_10V; C_1206_3216Metric
C_SS1: 10nF_TBD; C_0603_1608Metric
D1: SMBJ18CA; D_SMB
D_BUCK1: PDS760-13; D_PowerDI-5; MPN PDS760-13
D_LED1: Green_PowerGood; LED_0805_2012Metric
D_LED2: Green_3V3Present; LED_0805_2012Metric
F1: Polyfuse_5A; Fuse_1812_4532Metric
F2: Polyfuse_4A; Fuse_1812_4532Metric
J1: PWR JACK; PinHeader_1x04_P2.54mm_Vertical
J2: Barrel_Jack_Switch
J_OUT1: M12_5P; PinHeader_1x04_P2.54mm_Vertical
J_USB1: USB-C_Programming; USB_C_Receptacle_HRO_TYPE-C-31-M-12
L1: 3.3uH_TBD; L_Bourns-SRN6028
L2: 2.2uH_TBD; L_Bourns-SRN4018
Q1: IPD50N06S4L-16; SOT-23
R_CC1_1, R_CC2_1: 5.1k; R_0805_2012Metric
R_COMP1: 10k_TBD; R_0805_2012Metric
R_EN1A1: 73.2k_TBD; R_0805_2012Metric
R_EN1B1: 10k; R_0805_2012Metric
R_EN2: 100k; R_0805_2012Metric
R_FB1A1: 52.3k; R_0805_2012Metric
R_FB1B1, R_FB2B1: 10k; R_0805_2012Metric
R_FB2A1: 32.4k; R_0805_2012Metric
R_FLT1: 10k; R_0805_2012Metric
R_ILIM1: 20k_TBD; R_0805_2012Metric
R_IMON1: 10k; R_0805_2012Metric
R_LED1: 1k; R_0805_2012Metric
R_LED2: 330; R_0805_2012Metric
R_OVP1: 124k; R_0805_2012Metric
R_OVP2: 10k; R_0805_2012Metric
R_PG1: 10k; R_0805_2012Metric
R_RT1: 100k_TBD; R_0805_2012Metric
R_SHDN1: 100k; R_0805_2012Metric
R_UVLO1: 64.9k; R_0805_2012Metric
R_UVLO2: 10k; R_0805_2012Metric
R_gate1: 10k; R_0805_2012Metric
TP_3V3: V3V3_RAIL; TestPoint_Pad_D1.5mm
TP_5V1: V5_RAIL; TestPoint_Pad_D1.5mm
TP_12V_SW1: V12_SW; TestPoint_Pad_D1.5mm
TP_FLT1: nFLT; TestPoint_Pad_D1.5mm
TP_GND1: GND; TestPoint_Pad_D1.5mm
TP_IMON1: IMON; TestPoint_Pad_D1.5mm
TP_PG1: nPWRGD; TestPoint_Pad_D1.5mm
TP_USBVBUS1: USB_VBUS; TestPoint_Pad_D1.5mm
TP_VALVE_PWR1: V12_VALVE; TestPoint_Pad_D1.5mm
U1: TPS26600PWP; HTSSOP-16-1EP_4.4x5mm_P0.65mm_EP3.4x5mm_Mask2.66x2.46mm_The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
U2: TPS54561; WSON-10-1EP_4x4mm_P0.8mm_EP2.6x3mm_ThermalVias
U3: TPS563201; SOT-23-6

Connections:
12V_SW: C_IN2.1, C_OUT1.1, R_EN1A1.1, R_FLT1.2, TP_12V_SW1.1 (1_1), U1.15 (OUT), U1.16 (OUT), U2.2 (VIN)
+3V3: C_OUT3.1, D_LED2.1 (K), L2.2, R_FB2A1.1, TP_3V3.1 (1_1); also elsewhere on the board
+5V: C_IN3.1, C_OUT2.1, L1.2, R_EN2.1, R_FB1A1.1, R_LED1.2, R_PG1.1, TP_5V1.1 (1_1), U3.3 (VIN); also elsewhere on the board
+12V: F2.2, TP_VALVE_PWR1.1 (1_1); also elsewhere on the board
/Power/DC_IN_RAW_N: J1.2, Q1.3 (D)
/Power/DC_IN_RAW_P: F1.1, J1.1
/Power/SW: C_BOOT1.2, D_BUCK1.1 (K), L1.1, U2.9 (SW)
/Power/net_CC1: J_USB1.A5 (CC1), R_CC1_1.1
/Power/net_CC2: J_USB1.B5 (CC2), R_CC2_1.1
/Power/net_Q1G: Q1.1 (G), R_gate1.2
/Power/net_USB_VBUS: J_USB1.A4 (VBUS), J_USB1.A9 (VBUS), J_USB1.B4 (VBUS), J_USB1.B9 (VBUS), TP_USBVBUS1.1 (1_1)
GND: C_COMP1.2, C_DVDT1.2, C_IN1.2, C_IN2.2, C_IN3.2, C_OUT1.2, C_OUT2.2, C_OUT3.2, C_SS1.2, D1.2 (A2), D_BUCK1.2 (A), J1.3, J_OUT1.2, J_OUT1.3, J_USB1.A1 (GND), J_USB1.A12 (GND), J_USB1.B1 (GND), J_USB1.B12 (GND), J_USB1.SH (SHIELD), Q1.2 (S), R_CC1_1.2, R_CC2_1.2, R_EN1B1.2, R_FB1B1.2, R_FB2B1.2, R_ILIM1.2, R_IMON1.2, R_LED2.2, R_OVP2.2, R_RT1.2, R_UVLO2.2, TP_GND1.1 (1_1), U1.6 (MODE), U1.8 (RTN), U1.9 (GND), U1.17 (RTN), U2.8 (GND), U2.11 (GND), U3.1 (GND); also elsewhere on the board
unnamed: C_COMP1.1, R_COMP1.2
unnamed: D_LED1.2 (A), R_LED1.1
unnamed: D_LED1.1 (K), R_PG1.2, TP_PG1.1 (1_1), U2.10 (PWRGD)
unnamed: D_LED2.2 (A), R_LED2.1
unnamed: R_ILIM1.1, U1.11 (ILIM)
unnamed: R_IMON1.1, TP_IMON1.1 (1_1), U1.10 (IMON)
unnamed: R_OVP1.2, R_OVP2.1, U1.5 (OVP)
unnamed: R_UVLO1.2, R_UVLO2.1, U1.3 (UVLO)
unnamed: C_DVDT1.1, U1.12 (dVdT)
unnamed: R_FLT1.1, TP_FLT1.1 (1_1), U1.14 (~FLT)
unnamed: R_SHDN1.2, U1.7 (~SHDN)
unnamed: C_BOOT1.1, U2.1 (BOOT)
unnamed: R_COMP1.1, U2.7 (COMP)
unnamed: R_EN1A1.2, R_EN1B1.1, U2.3 (EN)
unnamed: R_FB1A1.2, R_FB1B1.1, U2.6 (FB)
unnamed: R_RT1.1, U2.5 (RT/CLK)
unnamed: C_SS1.1, U2.4 (SS/TR)
unnamed: R_EN2.2, U3.5 (EN)
unnamed: C_BOOT2.2, L2.1, U3.2 (SW)
unnamed: C_BOOT2.1, U3.6 (VBST)
unnamed: R_FB2A1.2, R_FB2B1.1, U3.4 (VFB)
VIN_12V: C_IN1.1, D1.1 (A1), F1.2, F2.1, J_OUT1.1, R_OVP1.1, R_SHDN1.1, R_UVLO1.1, R_gate1.1, U1.1 (IN), U1.2 (IN)
net_USB_DM: J_USB1.A7 (D-), J_USB1.B7 (D-); also elsewhere on the board
net_USB_DP: J_USB1.A6 (D+), J_USB1.B6 (D+); also elsewhere on the board
